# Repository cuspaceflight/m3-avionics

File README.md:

# Martlet III Avionics

This repository contains all the avionics for Martlet 3, including system 
design, documentation, schematics, PCBs, and firmware.

All work within is Copyright (c) 2017 Cambridge University Spaceflight unless identified otherwise in a specific declaration.

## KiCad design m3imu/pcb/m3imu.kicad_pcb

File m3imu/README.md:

# Martlet 3 Inertial Measurement Unit

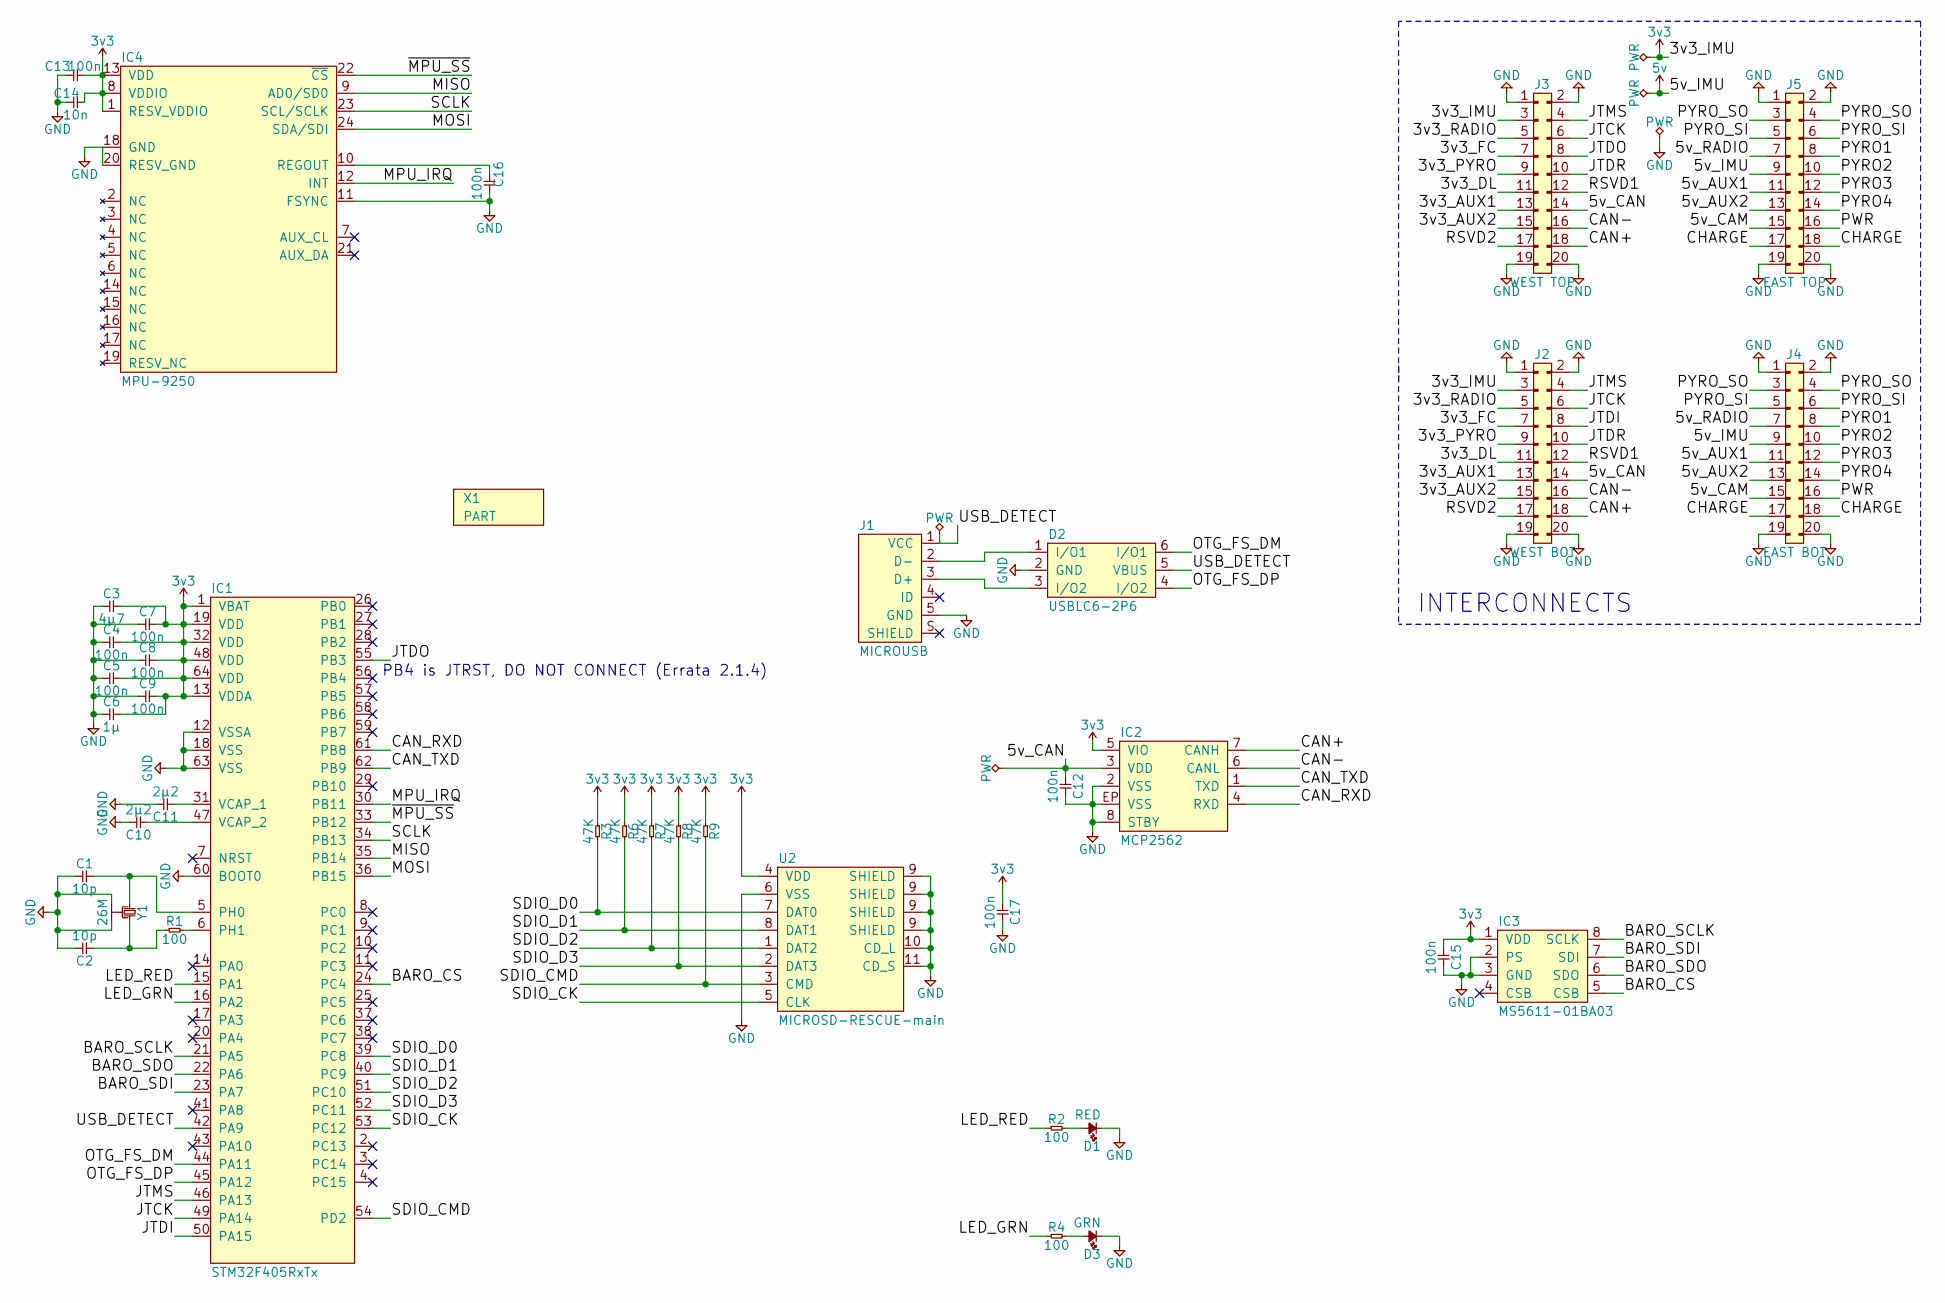
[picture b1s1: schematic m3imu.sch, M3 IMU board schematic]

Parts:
C1, C2: 10p; 0402; Farnell 2496790
C3: 4µ7; 0402; Farnell 2426952
C4, C5, C7, C8, C9, C12, C13, C15, C16, C17: 100n; 0402; Farnell 2496771
C6: 1µ; 0402; Farnell 2496814
C10, C11: 2µ2; 0402; Farnell 2362088
C14: 10n; 0402; Farnell 1414575
D1: RED; 0603-LED; Farnell 2314404
D2: USBLC6-2P6; SOT-666; Farnell 1295310
D3: GRN; 0603-LED; Farnell 2290363
IC1: STM32F405RxTx; LQFP-64; Farnell 2064363
IC2: MCP2562; DFN-8-EP-MICROCHIP; Farnell 2448755
IC3: MS5611-01BA03; MS5611; Farnell 2362662
IC4: MPU-9250; QFN-24-MPU9250; DigiKey 1428-1019-1-ND
J1: MICROUSB; MICROUSB_MOLEX_47589-0001; Farnell 1568023
J2: WEST BOT; SFML-110-02-L-D-LC
J3: WEST TOP; TFML-110-02-L-D
J4: EAST BOT; SFML-110-02-L-D-LC
J5: EAST TOP; TFML-110-02-L-D
R1, R2, R4: 100; 0402; Farnell 9239111
R3, R6, R7, R8, R9: 47K; 0603; Farnell 9238689
U2: MICROSD-RESCUE-main; MICROSD_MOLEX_503398-1892; Farnell 2358234
X1: PART; cusf_logo_small
Y1: 26M; XTAL-20x16; Farnell 2506952

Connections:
3v3: C3.2, C4.2, C5.2, C6.2, C7.2, C8.2, C9.2, C13.2, C14.2, C15.1, C17.1, IC1.1 (VBAT), IC1.13 (VDDA), IC1.19 (VDD), IC1.32 (VDD), IC1.48 (VDD), IC1.64 (VDD), IC2.5 (VIO), IC3.1 (VDD), IC4.1 (RESV_VDDIO), IC4.8 (VDDIO), IC4.13 (VDD), J2.3, J3.3, R3.1, R6.1, R7.1, R8.1, R9.1, U2.4 (VDD)
5v: J4.9, J5.9
/3v3_AUX1: J2.13, J3.13
/3v3_AUX2: J2.15, J3.15
/3v3_DL: J2.11, J3.11
/3v3_FC: J2.7, J3.7
/3v3_PYRO: J2.9, J3.9
/3v3_RADIO: J2.5, J3.5
/5v_AUX1: J4.11, J5.11
/5v_AUX2: J4.13, J5.13
/5v_CAM: J4.15, J5.15
/5v_CAN: C12.1, IC2.3 (VDD), J2.14, J3.14
/5v_RADIO: J4.7, J5.7
/BARO_CS: IC1.24 (PC4), IC3.5 (CSB)
/BARO_SCLK: IC1.21 (PA5), IC3.8 (SCLK)
/BARO_SDI: IC1.23 (PA7), IC3.7 (SDI)
/BARO_SDO: IC1.22 (PA6), IC3.6 (SDO)
/CAN+: IC2.7 (CANH), J2.18, J3.18
/CAN-: IC2.6 (CANL), J2.16, J3.16
/CAN_RXD: IC1.61 (PB8), IC2.4 (RXD)
/CAN_TXD: IC1.62 (PB9), IC2.1 (TXD)
/CHARGE: J4.17, J4.18, J5.17, J5.18
/JTCK: IC1.49 (PA14), J2.6, J3.6
/JTDI: IC1.50 (PA15), J2.8
/JTDO: IC1.55 (PB3), J3.8
/JTDR: J2.10, J3.10
/JTMS: IC1.46 (PA13), J2.4, J3.4
/LED_GRN: IC1.16 (PA2), R4.1
/LED_RED: IC1.15 (PA1), R2.1
/MISO: IC1.35 (PB14), IC4.9 (AD0/SD0)
/MOSI: IC1.36 (PB15), IC4.24 (SDA/SDI)
/MPU_IRQ: IC1.30 (PB11), IC4.12 (INT)
/OTG_FS_DM: D2.6 (I/O1), IC1.44 (PA11)
/OTG_FS_DP: D2.4 (I/O2), IC1.45 (PA12)
/PWR: J4.16, J5.16
/PYRO1: J4.8, J5.8
/PYRO2: J4.10, J5.10
/PYRO3: J4.12, J5.12
/PYRO4: J4.14, J5.14
/PYRO_SI: J4.5, J4.6, J5.5, J5.6
/PYRO_SO: J4.3, J4.4, J5.3, J5.4
/RSVD1: J2.12, J3.12
/RSVD2: J2.17, J3.17
/SCLK: IC1.34 (PB13), IC4.23 (SCL/SCLK)
/SDIO_CK: IC1.53 (PC12), U2.5 (CLK)
/SDIO_CMD: IC1.54 (PD2), R9.2, U2.3 (CMD)
/SDIO_D0: IC1.39 (PC8), R3.2, U2.7 (DAT0)
/SDIO_D1: IC1.40 (PC9), R6.2, U2.8 (DAT1)
/SDIO_D2: IC1.51 (PC10), R7.2, U2.1 (DAT2)
/SDIO_D3: IC1.52 (PC11), R8.2, U2.2 (DAT3)
/USB_DETECT: D2.5 (VBUS), IC1.42 (PA9), J1.1 (VCC)
/~MPU_SS: IC1.33 (PB12), IC4.22 (~CS)
GND: C1.1, C2.2, C3.1, C4.1, C5.1, C6.1, C7.1, C8.1, C9.1, C10.2, C11.2, C12.2, C13.1, C14.1, C15.2, C16.2, C17.2, D1.1, D2.2 (GND), D3.1, IC1.12 (VSSA), IC1.18 (VSS), IC1.60 (BOOT0), IC1.63 (VSS), IC2.2 (VSS), IC2.8 (STBY), IC2.EP (VSS), IC3.2 (PS), IC3.3 (GND), IC4.11 (FSYNC), IC4.18 (GND), IC4.20 (RESV_GND), J1.5 (GND), J2.1, J2.2, J2.19, J2.20, J3.1, J3.2, J3.19, J3.20, J4.1, J4.2, J4.19, J4.20, J5.1, J5.2, J5.19, J5.20, U2.6 (VSS), U2.9 (SHIELD), U2.10 (CD_L), U2.11 (CD_S), Y1.2, Y1.4
unnamed: C1.2, IC1.5 (PH0), Y1.1
unnamed: C2.1, R1.1, Y1.3
unnamed: C10.1, IC1.47 (VCAP_2)
unnamed: C11.1, IC1.31 (VCAP_1)
unnamed: C16.1, IC4.10 (REGOUT)
unnamed: D1.2, R2.2
unnamed: D2.1 (I/O1), J1.2 (D-)
unnamed: D2.3 (I/O2), J1.3 (D+)
unnamed: D3.2, R4.2
unnamed: IC1.6 (PH1), R1.2

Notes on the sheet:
INTERCONNECTS
PB4 is JTRST, DO NOT CONNECT (Errata 2.1.4)

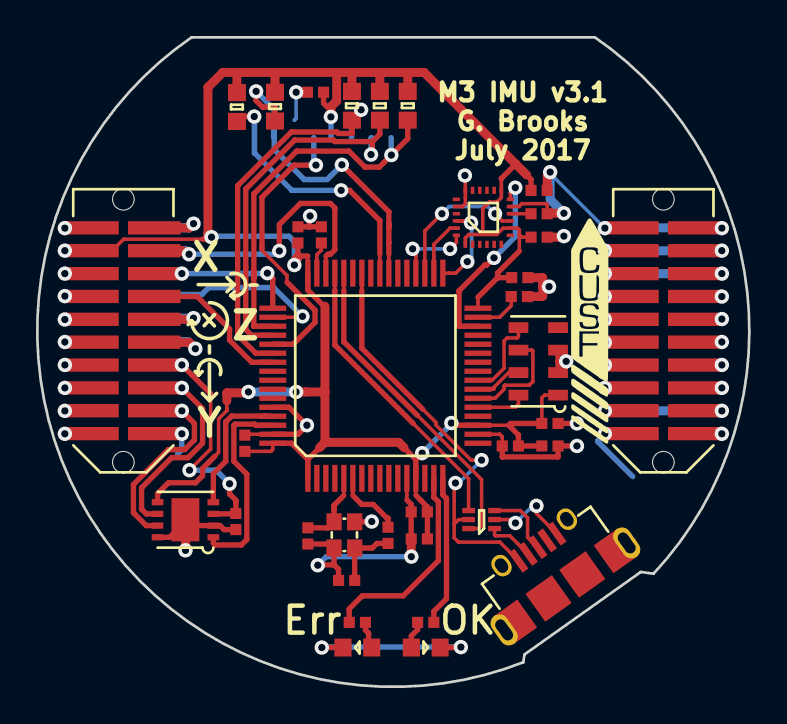
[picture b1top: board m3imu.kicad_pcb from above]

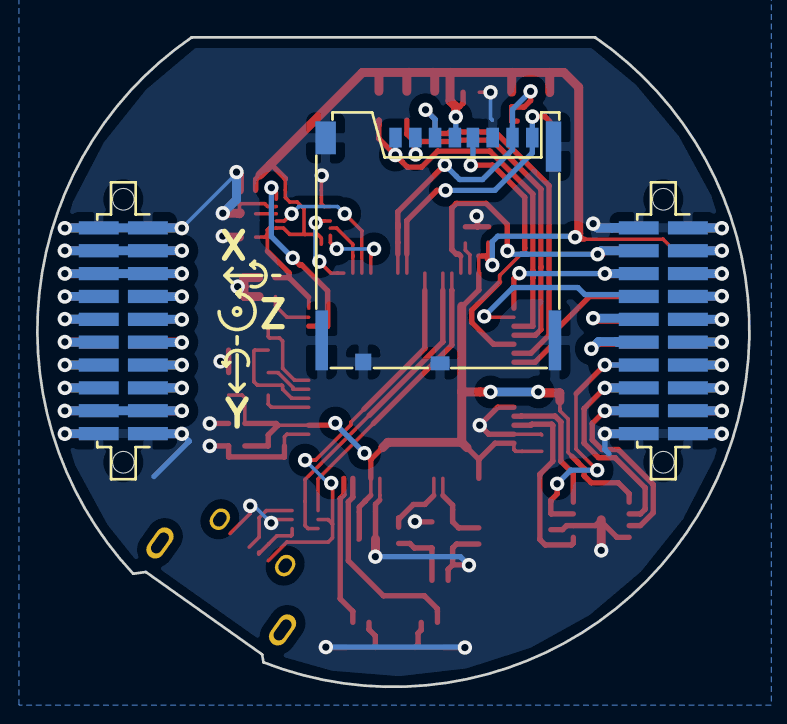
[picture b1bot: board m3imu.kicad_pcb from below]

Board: 2 copper layers, 39.6 x 36.1 mm, 40 parts (3 on the bottom side), 63 nets.

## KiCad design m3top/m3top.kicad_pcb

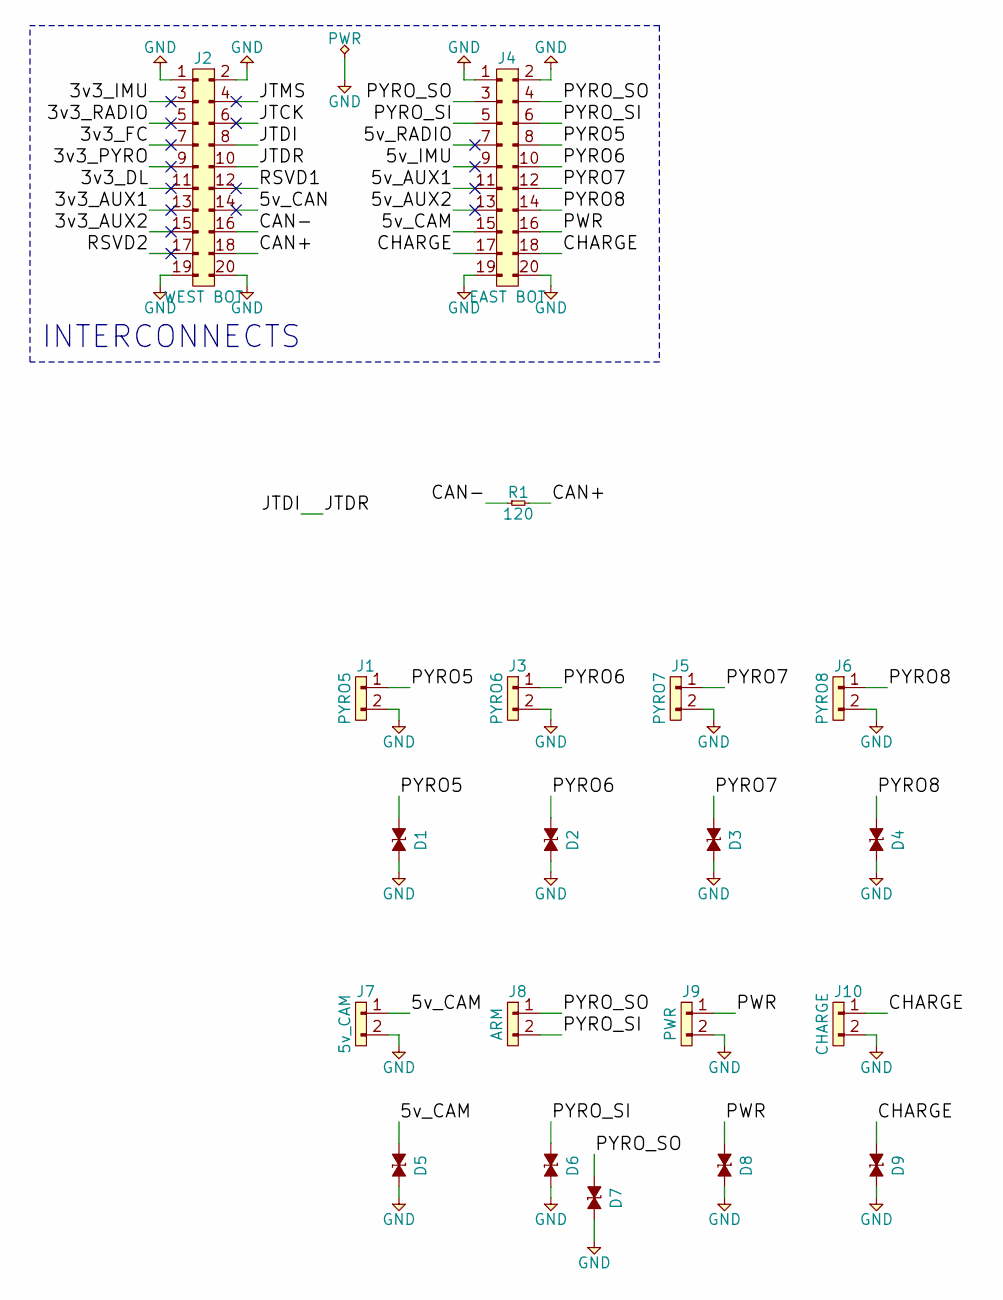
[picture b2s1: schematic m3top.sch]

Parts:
D1, D2, D3, D4, D5, D6, D7, D8, D9: ESD_DIODE; 0402; Farnell 2368169
J1: PYRO5; B02B-PASK; Farnell 1830734
J2: WEST BOT; SFML-110-02-L-D-LC
J3: PYRO6; B02B-PASK; Farnell 1830734
J4: EAST BOT; SFML-110-02-L-D-LC
J5: PYRO7; B02B-PASK; Farnell 1830734
J6: PYRO8; B02B-PASK; Farnell 1830734
J7: 5v_CAM; B02B-PASK; Farnell 1830734
J8: ARM; B02B-PASK; Farnell 1830734
J9: PWR; B02B-PASK; Farnell 1830734
J10: CHARGE; B02B-PASK; Farnell 1830734
R1: 120; 0603

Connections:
/3v3_AUX1: J2.13
/3v3_AUX2: J2.15
/3v3_DL: J2.11
/3v3_FC: J2.7
/3v3_IMU: J2.3
/3v3_PYRO: J2.9
/3v3_RADIO: J2.5
/5v_AUX1: J4.11
/5v_AUX2: J4.13
/5v_CAM: D5.1, J4.15, J7.1
/5v_CAN: J2.14
/5v_IMU: J4.9
/5v_RADIO: J4.7
/CAN+: J2.18, R1.2
/CAN-: J2.16, R1.1
/CHARGE: D9.1, J4.17, J4.18, J10.1
/JTCK: J2.6
/JTDI: J2.8, J2.10
/JTMS: J2.4
/PWR: D8.1, J4.16, J9.1
/PYRO5: D1.1, J1.1, J4.8
/PYRO6: D2.1, J3.1, J4.10
/PYRO7: D3.1, J4.12, J5.1
/PYRO8: D4.1, J4.14, J6.1
/PYRO_SI: D6.1, J4.5, J4.6, J8.2
/PYRO_SO: D7.1, J4.3, J4.4, J8.1
/RSVD1: J2.12
/RSVD2: J2.17
GND: D1.2, D2.2, D3.2, D4.2, D5.2, D6.2, D7.2, D8.2, D9.2, J1.2, J2.1, J2.2, J2.19, J2.20, J3.2, J4.1, J4.2, J4.19, J4.20, J5.2, J6.2, J7.2, J9.2, J10.2

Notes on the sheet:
INTERCONNECTS

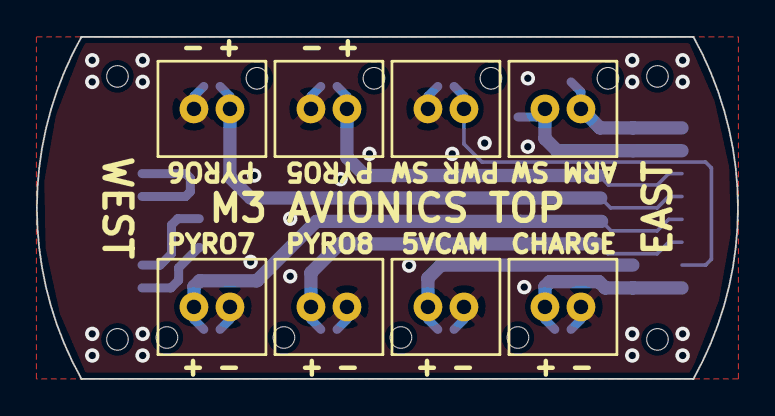
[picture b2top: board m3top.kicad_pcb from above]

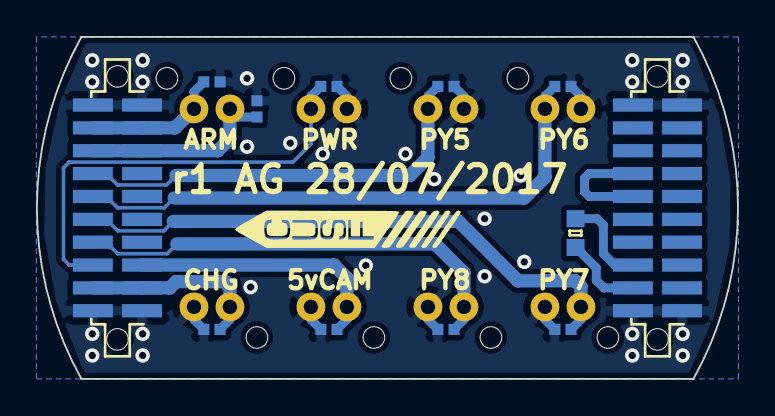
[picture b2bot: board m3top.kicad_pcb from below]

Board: 2 copper layers, 38.9 x 19.0 mm, 20 parts (12 on the bottom side), 13 nets.

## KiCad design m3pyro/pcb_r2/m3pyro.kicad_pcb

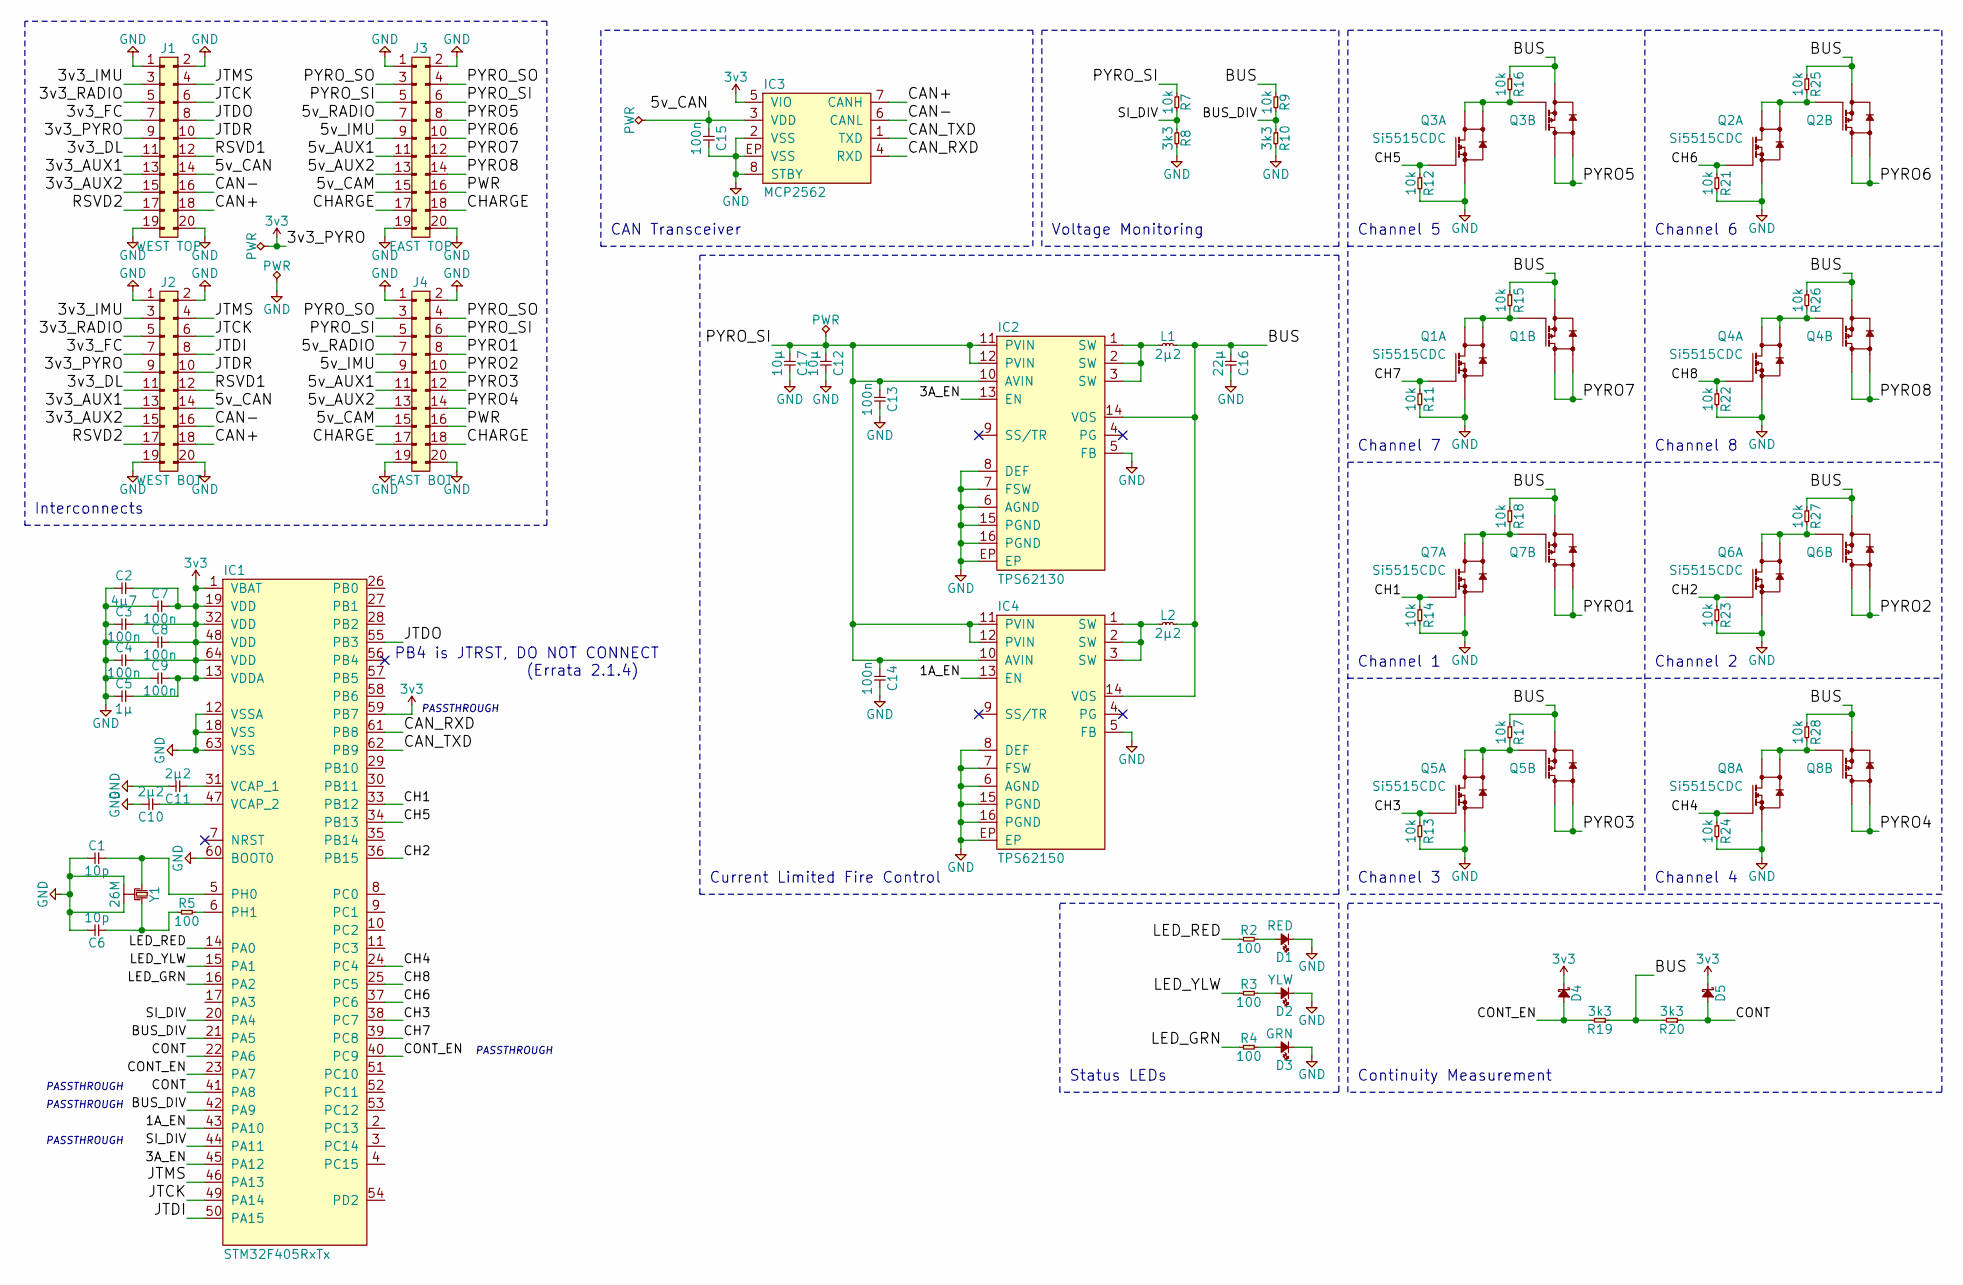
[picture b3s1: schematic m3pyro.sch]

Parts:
C1, C6: 10p; 0402; Farnell 2496790
C2: 4µ7; 0402; Farnell 2426952
C3, C4, C7, C8, C9, C15: 100n; 0402; Farnell 2496771
C5: 1µ; 0402; Farnell 2496814
C10, C11: 2µ2; 0402; Farnell 2362088
C12, C17: 10µ; 0603
C13, C14: 100n; 0402
C16: 22µ; 0603
D1: RED; 0603-LED; Farnell 2314404
D2: YLW; 0603-LED; Farnell 2335804
D3: GRN; 0603-LED; Farnell 2290363
D4, D5: PMEG2005AEA; SOD-323; Farnell 8737843
IC1: STM32F405RxTx; LQFP-64; Farnell 2064363
IC2: TPS62130; QFN-16-EP-TI; Farnell 2361246
IC3: MCP2562; DFN-8-EP-MICROCHIP; Farnell 2448755
IC4: TPS62150; QFN-16-EP-TI; Farnell 2361248
J1: WEST TOP; TFML-110-02-L-D
J2: WEST BOT; SFML-110-02-L-D-LC
J3: EAST TOP; TFML-110-02-L-D
J4: EAST BOT; SFML-110-02-L-D-LC
L1, L2: 2µ2; XFL4020; Farnell 2289216
Q1, Q2, Q3, Q4, Q5, Q6, Q7, Q8: Si5515CDC; ChipFET-1206-8; Farnell 2335332
R2, R3, R4, R5: 100; 0402; Farnell 9239111
R7, R9, R11, R12, R13, R14, R15, R16, R17, R18, R21, R22, R23, R24, R25, R26, R27, R28: 10k; 0402
R8, R10, R19, R20: 3k3; 0402
Y1: 26M; XTAL-20x16; Farnell 2506952

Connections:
3v3: C2.2, C3.2, C4.2, C5.2, C7.2, C8.2, C9.2, D4.1, D5.1, IC1.1 (VBAT), IC1.13 (VDDA), IC1.19 (VDD), IC1.32 (VDD), IC1.48 (VDD), IC1.59 (PB7), IC1.64 (VDD), IC3.5 (VIO), J1.9, J2.9
/1A_EN: IC1.43 (PA10), IC4.13 (EN)
/3A_EN: IC1.45 (PA12), IC2.13 (EN)
/3v3_AUX1: J1.13, J2.13
/3v3_AUX2: J1.15, J2.15
/3v3_DL: J1.11, J2.11
/3v3_FC: J1.7, J2.7
/3v3_IMU: J1.3, J2.3
/3v3_RADIO: J1.5, J2.5
/5v_AUX1: J3.11, J4.11
/5v_AUX2: J3.13, J4.13
/5v_CAM: J3.15, J4.15
/5v_CAN: C15.1, IC3.3 (VDD), J1.14, J2.14
/5v_IMU: J3.9, J4.9
/5v_RADIO: J3.7, J4.7
/BUS: C16.1, IC2.14 (VOS), IC4.14 (VOS), L1.2, L2.2, Q1.3 (S2), Q2.3 (S2), Q3.3 (S2), Q4.3 (S2), Q5.3 (S2), Q6.3 (S2), Q7.3 (S2), Q8.3 (S2), R9.1, R15.1, R16.1, R17.1, R18.1, R19.1, R20.2, R25.1, R26.1, R27.1, R28.1
/BUS_DIV: IC1.21 (PA5), IC1.42 (PA9), R9.2, R10.1
/CAN+: IC3.7 (CANH), J1.18, J2.18
/CAN-: IC3.6 (CANL), J1.16, J2.16
/CAN_RXD: IC1.61 (PB8), IC3.4 (RXD)
/CAN_TXD: IC1.62 (PB9), IC3.1 (TXD)
/CH1: IC1.33 (PB12), Q7.2 (G1), R14.1
/CH2: IC1.36 (PB15), Q6.2 (G1), R23.1
/CH3: IC1.38 (PC7), Q5.2 (G1), R13.1
/CH4: IC1.24 (PC4), Q8.2 (G1), R24.1
/CH5: IC1.34 (PB13), Q3.2 (G1), R12.1
/CH6: IC1.37 (PC6), Q2.2 (G1), R21.1
/CH7: IC1.39 (PC8), Q1.2 (G1), R11.1
/CH8: IC1.25 (PC5), Q4.2 (G1), R22.1
/CHARGE: J3.17, J3.18, J4.17, J4.18
/CONT: D5.2, IC1.22 (PA6), IC1.41 (PA8), R20.1
/CONT_EN: D4.2, IC1.23 (PA7), IC1.40 (PC9), R19.2
/JTCK: IC1.49 (PA14), J1.6, J2.6
/JTDI: IC1.50 (PA15), J2.8
/JTDO: IC1.55 (PB3), J1.8
/JTDR: J1.10, J2.10
/JTMS: IC1.46 (PA13), J1.4, J2.4
/LED_GRN: IC1.16 (PA2), R4.1
/LED_RED: IC1.14 (PA0), R2.1
/LED_YLW: IC1.15 (PA1), R3.1
/PWR: J3.16, J4.16
/PYRO1: J4.8, Q7.5 (D2), Q7.6 (D2)
/PYRO2: J4.10, Q6.5 (D2), Q6.6 (D2)
/PYRO3: J4.12, Q5.5 (D2), Q5.6 (D2)
/PYRO4: J4.14, Q8.5 (D2), Q8.6 (D2)
/PYRO5: J3.8, Q3.5 (D2), Q3.6 (D2)
/PYRO6: J3.10, Q2.5 (D2), Q2.6 (D2)
/PYRO7: J3.12, Q1.5 (D2), Q1.6 (D2)
/PYRO8: J3.14, Q4.5 (D2), Q4.6 (D2)
/PYRO_SI: C12.1, C13.1, C14.1, C17.1, IC2.10 (AVIN), IC2.11 (PVIN), IC2.12 (PVIN), IC4.10 (AVIN), IC4.11 (PVIN), IC4.12 (PVIN), J3.5, J3.6, J4.5, J4.6, R7.1
/PYRO_SO: J3.3, J3.4, J4.3, J4.4
/RSVD1: J1.12, J2.12
/RSVD2: J1.17, J2.17
/SI_DIV: IC1.20 (PA4), IC1.44 (PA11), R7.2, R8.1
GND: C1.1, C2.1, C3.1, C4.1, C5.1, C6.2, C7.1, C8.1, C9.1, C10.2, C11.2, C12.2, C13.2, C14.2, C15.2, C16.2, C17.2, D1.1, D2.1, D3.1, IC1.12 (VSSA), IC1.18 (VSS), IC1.60 (BOOT0), IC1.63 (VSS), IC2.5 (FB), IC2.6 (AGND), IC2.7 (FSW), IC2.8 (DEF), IC2.15 (PGND), IC2.16 (PGND), IC2.EP, IC3.2 (VSS), IC3.8 (STBY), IC3.EP (VSS), IC4.5 (FB), IC4.6 (AGND), IC4.7 (FSW), IC4.8 (DEF), IC4.15 (PGND), IC4.16 (PGND), IC4.EP, J1.1, J1.2, J1.19, J1.20, J2.1, J2.2, J2.19, J2.20, J3.1, J3.2, J3.19, J3.20, J4.1, J4.2, J4.19, J4.20, Q1.1 (S1), Q2.1 (S1), Q3.1 (S1), Q4.1 (S1), Q5.1 (S1), Q6.1 (S1), Q7.1 (S1), Q8.1 (S1), R8.2, R10.2, R11.2, R12.2, R13.2, R14.2, R21.2, R22.2, R23.2, R24.2, Y1.2, Y1.4
unnamed: C1.2, IC1.5 (PH0), Y1.1
unnamed: C6.1, R5.1, Y1.3
unnamed: C10.1, IC1.47 (VCAP_2)
unnamed: C11.1, IC1.31 (VCAP_1)
unnamed: D1.2, R2.2
unnamed: D2.2, R3.2
unnamed: D3.2, R4.2
unnamed: IC1.6 (PH1), R5.2
unnamed: IC2.1 (SW), IC2.2 (SW), IC2.3 (SW), L1.1
unnamed: IC4.1 (SW), IC4.2 (SW), IC4.3 (SW), L2.1
unnamed: Q1.4 (G2), Q1.7 (D1), Q1.8 (D1), R15.2
unnamed: Q2.4 (G2), Q2.7 (D1), Q2.8 (D1), R25.2
unnamed: Q3.4 (G2), Q3.7 (D1), Q3.8 (D1), R16.2
unnamed: Q4.4 (G2), Q4.7 (D1), Q4.8 (D1), R26.2
unnamed: Q5.4 (G2), Q5.7 (D1), Q5.8 (D1), R17.2
unnamed: Q6.4 (G2), Q6.7 (D1), Q6.8 (D1), R27.2
unnamed: Q7.4 (G2), Q7.7 (D1), Q7.8 (D1), R18.2
unnamed: Q8.4 (G2), Q8.7 (D1), Q8.8 (D1), R28.2

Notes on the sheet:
Interconnects
PB4 is JTRST, DO NOT CONNECT (Errata 2.1.4)
Channel 5
Channel 6
Channel 7
Channel 8
Channel 1
Channel 2
Channel 3
Channel 4
Continuity Measurement
Voltage Monitoring
Current Limited Fire Control
CAN Transceiver
Status LEDs
PASSTHROUGH

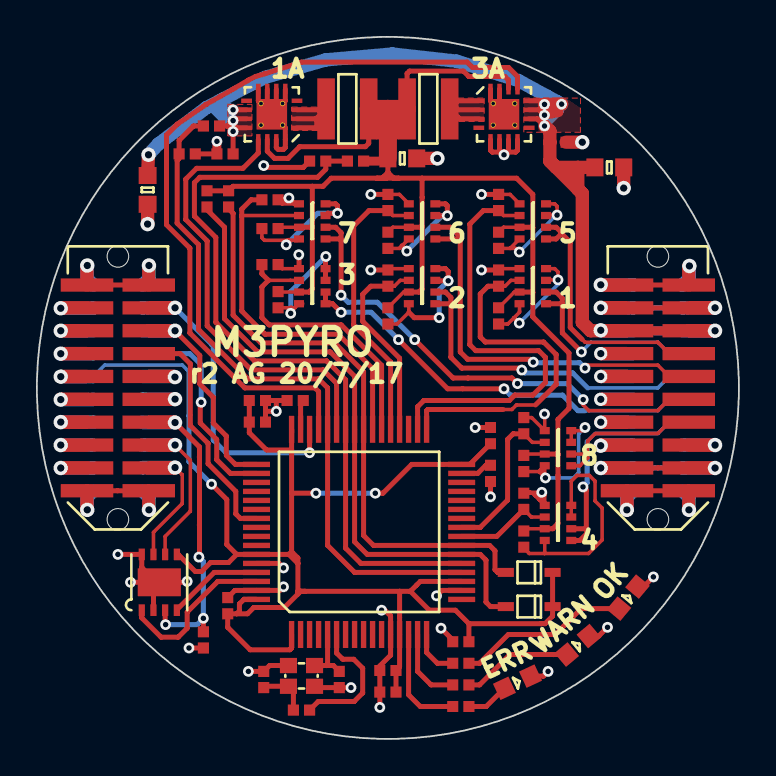
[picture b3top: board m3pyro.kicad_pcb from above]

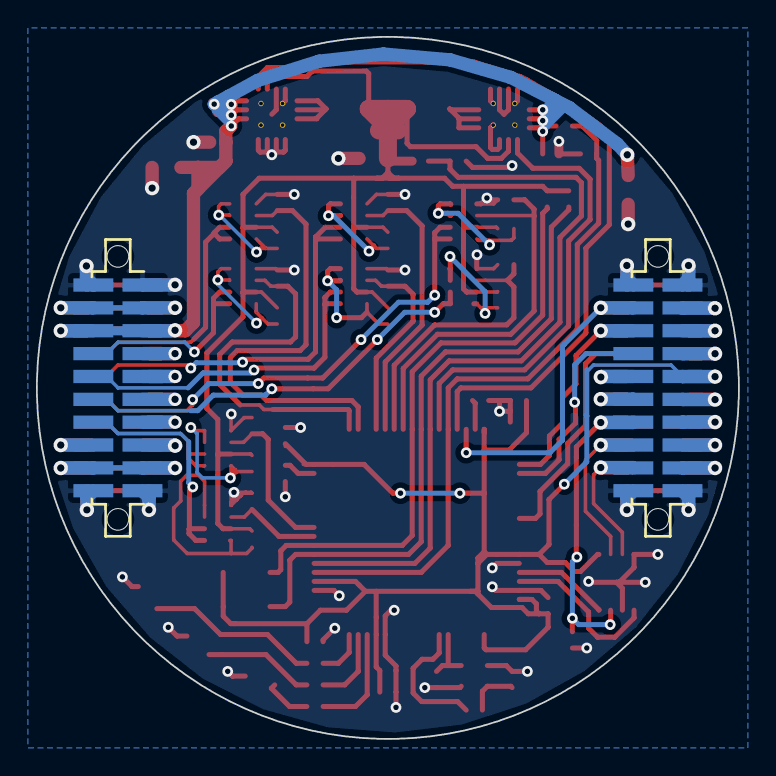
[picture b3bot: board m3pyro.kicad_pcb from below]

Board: 2 copper layers, 39.0 x 39.0 mm, 67 parts (2 on the bottom side), 73 nets.

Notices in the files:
TOAD/firmware/board.h:
ChibiOS - Copyright (C) 2006..2016 Giovanni Di Sirio
Licensed under the Apache License, Version 2.0 (the "License");
